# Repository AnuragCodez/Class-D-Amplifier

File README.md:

# **Self-Oscillating Class D Amplifier using the LM311 and IR2153**

### **Main Idea**

1. **The "Brain" (U2 - LM311)**
   This is the main modulator. It works like a comparator. It looks at two signals:

   * The low-level audio input (from J1).
   * A feedback signal that comes straight from the high-power speaker output (OUT).
     This comparison makes the Pulse Width Modulated (PWM) signal. The circuit oscillates by itself at a very high frequency (250–400 kHz) because the output is "fed back" to the input.

2. **The "Translator" (VT1 - 2N5401)**
   The LM311's output signal is not at the right voltage level to directly control the IR2153. VT1 changes the level of the IR2153's timing pin in response to the LM311's PWM signal.

3. **The "Driver" (U3 - IR2153)**
   This is the "muscle" that makes the main switches work. This is a strong half-bridge driver that does a number of important things:

   * It gives the MOSFETs the high-current pulses they need to turn on and off quickly.
   * It automatically creates the dead time needed between switches to stop shoot-through.
   * It has the bootstrap circuit (with VD2 and C10) that the high-side MOSFET needs to work.

4. **The "Muscle" (VT3, VT4 - MOSFETs)**
   This is the half-bridge with a lot of power. It gets signals from the IR2153 and "chops" the main 45V supply to make the high-power PWM signal.

5. **The "Voice" (L1, C18 - Filter)**
   This is the last LC low-pass filter. It gets rid of the high-frequency switching noise (about 300 kHz) and leaves only the amplified, low-frequency audio signal (less than 20 kHz) to power your speaker.

---

## **2. Component Selection Logic**

| **Component(s)**        | **Role**               | **Selection Logic**                                                                                                                                                                                                                                     |
| ----------------------- | ---------------------- | ------------------------------------------------------------------------------------------------------------------------------------------------------------------------------------------------------------------------------------------------------- |
| **U1 (LM311)**          | Comparator             | We need a quick way to compare high-frequency oscillation. The LM311 is a classic, high-speed, and stable choice, far superior to a standard op-amp (like a 741 or 358) for this task.                                                                  |
| **U3 (IR2153)**         | MOSFET Gate Driver     | This is the core of the power stage. It is chosen because it's robust half-bridge driver. It makes the design a lot easier by taking care of dead time and high-side bootstrap driving on its own.                                                      |
| **VT3, VT4 (IRF640)**   | Power MOSFETs          | These are the main switches. The IRF640 is a good choice as it has a 200V rating (safe for a +45V supply, which is 90V total) and low "on-resistance" for high efficiency.                                                                              |
| **VT1 (2N5401)**        | Level-Shifter          | A basic, high-voltage PNP transistor that connects the LM311's output to the IR2153's timing pin.                                                                                                                                                       |
| **L1**                  | Filter Inductor        | This inductor, along with C18, forms the low-pass filter. It must be a power inductor that can handle the full output current without saturating.                                                                                                       |
| **C18**                 | Filter Capacitor       | This capacitor sends the noise from the switch to the ground. It has to be a film capacitor. A ceramic or electrolytic cap would work very poorly, get hot, and make things sound distorted.                                                            |
| **C10, VD2**            | Bootstrap Circuit      | C10 is the "flying" capacitor that stores charge for the high-side driver. The diode that charges it is VD2. VD2 has to be a fast diode.                                                                                                                |
| **R12, R13**            | Gate Resistors         | These are very important. They are not for limiting current. They are dampers that slow down the switching of the MOSFET just a little bit to stop high-frequency oscillations on the gate, which can break the MOSFET.                                 |
| **C11, C16, C17, etc.** | Main Bypass Capacitors | These are the most important parts for stability. They serve as local, high-current storage for the power stage. The power supply can't send high-speed current pulses, but they can. The most important rule for designing a PCB is where to put them. |

---

## **3. PCB Design and Layout Guide**

### **3.1. PCB Size and Layers**

* **Size:** Layout of approx. 120mm × 50mm compact size.
* **Layers:** 2-Layer (Top / Bottom). This is essential.

---

### **3.2. Component Placement**

#### **Block A: The "Quiet Zone" (Left Side)**

This is the amplifier's "brain" in analog form. The goal here is to keep noise out.

* **J1 (Audio Input):**
  **Where:** At the very left edge of the board.
  **Why:** It’s far from the noisy power section to avoid interference.

* **U2 (LM311 Comparator):**
  **Where:** In the middle of the quiet zone, near supporting components.
  **Why:** Keeps sensitive analog traces short and free from interference.

* **U1 (Voltage Regulator):**
  **Where:** Next to audio input (J1) and analog ICs (U2).
  **Why:** Provides a clean, stable power source for analog circuitry.

* **R3, R4, C4, C_T1, R_T1, etc.:**
  **Where:** Tightly grouped around U2.
  **Why:** Keeps critical modulator traces short to avoid noise coupling.

---

#### **Block B: The "Noisy" Power Zone (Right Side)**

Handles high currents and switching.

* **MOSFETs, C10, C11, C14–C17, J2 (Power Input):**
  **Why:** These form the “hot loop.” Keeping them close reduces inductance, voltage spikes, and EMI.

* **L1 (Inductor) and C18, C19 (Filter Caps):**
  **Where:** Far-right edge, before speaker output J4.
  **Why:** Prevents magnetic noise from coupling into sensitive input areas.

* **J3, J4 (Power & Speaker Outputs):**
  **Where:** At the end of the power zone.
  **Why:** Keeps high-current paths short and isolated.

---

#### **Block C: The "Bridge" (Middle Zone)**

Connects the brain and muscle.

* **U3 (IR2153 Gate Driver):**
  **Where:** Between U2 (LM311) and the MOSFETs.
  **Why:** Short, balanced routing to both the comparator and MOSFET gates.

* **R10, D5, D6, R11, R12 (Gate Resistors & Protection):**
  **Where:** Close to MOSFET gates.
  **Why:** Prevents gate ringing and ensures clean switching.

* **C13 (Bootstrap Capacitor):**
  **Where:** Very close to U3 and the high-side MOSFET.
  **Why:** Ensures short, low-inductance charging/discharging paths.

---

### **3.3. Trace Width and Routing**

#### **1. Signal Traces ("Thin" Traces)**

* **What They Are:** Low-power analog and logic signals (e.g., audio input, LM311 area, IR2153 timing).
* **Width:** 0.4 mm (≈16 mil)

---

#### **2. Gate Driver Traces (Medium Traces)**

* **What They Are:** IR2153 outputs (pins 5 & 7) to MOSFET gates.
* **Width:** 0.5 mm (≈20 mil)
* **Why:** To minimize inductance and ensure clean gate charging.

---

#### **3. Power Traces ("Thick" Traces)**

* **What They Are:** High-current, high-voltage connections — supply lines, switch node, and ground.
* **Width:** 0.6 mm (≈24 mil)
* **Why:** To safely carry several amperes continuously.

---

#### **4. The Ground (The Foundation)**

* **Design:** Use a solid copper pour on the entire bottom layer.
* **Purpose:** Provides a low-noise, low-inductance return path essential for Class D amplifier stability.

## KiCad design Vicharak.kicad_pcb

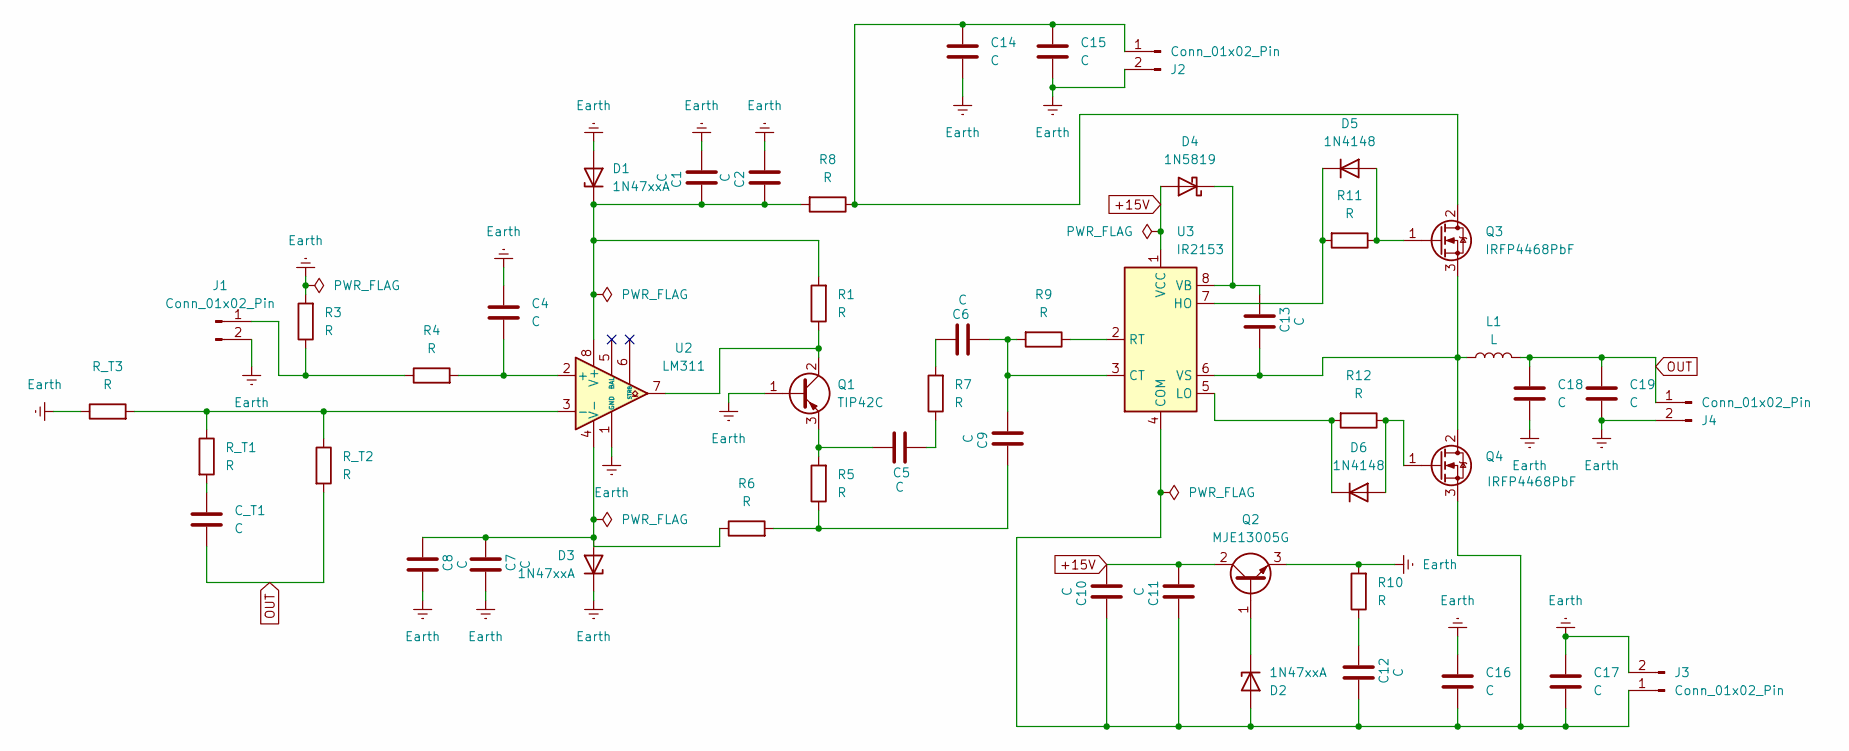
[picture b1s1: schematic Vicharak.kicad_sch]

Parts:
C1, C2, C4, C5, C6, C7, C8, C9, C10, C11, C12, C13, C14, C15, C16, C17, C18, C19: C; C_Radial_D6.3mm_H5.0mm_P2.50mm
C_T1: C; C_Radial_D6.3mm_H5.0mm_P2.50mm
D1, D2, D3: 1N47xxA; D_DO-41_SOD81_P10.16mm_Horizontal
D4: 1N5819; D_DO-41_SOD81_P10.16mm_Horizontal
D5, D6: 1N4148; D_DO-35_SOD27_P7.62mm_Horizontal
J1: Conn_01x02_Pin; PhoenixContact_GMSTBA_2,5_2-G_1x02_P7.50mm_Horizontal
J2, J3, J4: Conn_01x02_Pin; PhoenixContact_MCV_1,5_2-G-3.5_1x02_P3.50mm_Vertical
L1: L; L_7.3x7.3_H4.5
Q1: TIP42C; TO-220-3_Vertical
Q2: MJE13005G; TO-220-3_Vertical
Q3, Q4: IRFP4468PbF; TO-247-3_Vertical
R1, R3, R4, R5, R6, R7, R8, R9, R10, R11, R12: R; R_Axial_DIN0207_L6.3mm_D2.5mm_P2.54mm_Vertical
R_T1, R_T2, R_T3: R; R_Axial_DIN0207_L6.3mm_D2.5mm_P2.54mm_Vertical
U2: LM311; DIP-8_W7.62mm
U3: IR2153; DIP-8_W7.62mm

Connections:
+15V: C10.2, C11.2, D4.2 (A), Q2.2 (C), U3.1 (VCC)
Earth: C1.2, C2.2, C4.2, C7.2, C8.2, C14.2, C15.2, C16.1, C17.1, C18.2, C19.2, D1.2 (A), D3.1 (K), J1.2, J2.2, J3.2, J4.2, Q1.1 (B), Q2.3 (E), R3.2, R10.2, R_T3.1, U2.1 (GND)
unnamed: C5.1, R7.1
unnamed: C6.1, R7.2
unnamed: C9.1, R5.1, R6.2
unnamed: C12.1, R10.1
unnamed: C_T1.1, R_T1.2
unnamed: C1.1, C2.1, D1.1 (K), R1.2, R8.2, U2.8 (V+)
unnamed: C10.1, C11.1, C12.2, C16.2, C17.2, D2.2 (A), J3.1, Q4.3 (S), U3.4 (COM)
unnamed: D2.1 (K), Q2.1 (B)
unnamed: C7.1, C8.1, D3.2 (A), R6.1, U2.4 (V-)
unnamed: C13.1, D4.1 (K), U3.8 (VB)
unnamed: D5.2 (A), Q3.1 (G), R11.1
unnamed: D5.1 (K), R11.2, U3.7 (HO)
unnamed: D6.2 (A), Q4.1 (G), R12.1
unnamed: D6.1 (K), R12.2, U3.5 (LO)
unnamed: J1.1, R3.1, R4.1
unnamed: C14.1, C15.1, J2.1, Q3.2 (D), R8.1
unnamed: Q1.2 (C), R1.1, U2.7
unnamed: C5.2, Q1.3 (E), R5.2
unnamed: C13.2, L1.1, Q3.3 (S), Q4.2 (D), U3.6 (VS)
unnamed: C4.1, R4.2, U2.2 (+)
unnamed: R_T1.1, R_T2.1, R_T3.2, U2.3 (-)
unnamed: C6.2, C9.2, R9.2, U3.3 (CT)
unnamed: R9.1, U3.2 (RT)
OUT: C18.1, C19.1, C_T1.2, J4.1, L1.2, R_T2.2

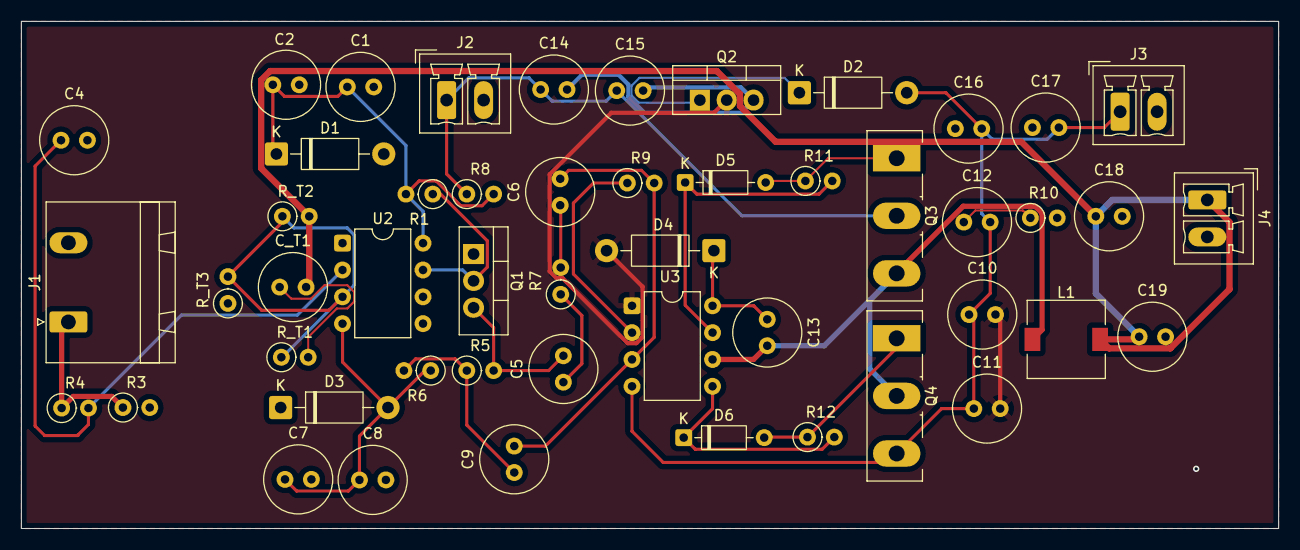
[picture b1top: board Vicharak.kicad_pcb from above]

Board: 2 copper layers, 119.0 x 48.0 mm, 50 parts (0 on the bottom side), 26 nets.
